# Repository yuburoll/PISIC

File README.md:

# PISIC
42-44key row staggered split keyboard with GRIN inspired layout, under 102mm PCB

The name PISIC means grin in korean, also is korean pun of grin layout of [ansic](https://github.com/yuburoll/ANSIC).

## Preparation

- 2x pro micro form factor dev board

- 2x PISIC PCB Boards, provided from the repo

- 1x printed case sets, 2 parts total, provided from the repo

- 2x 1.5-1.6T keyboard plates, provided from the repo

- 2x 1.5-1.6T back plates, provided from the repo

- 44x diodes

- 46x Kailh hotswap sockets (or compatibles)

- 24x M2x6 screws, flathead

- 2x PJ320A 1/8(3.5mm) TRRS connector

- 2x 4x4x1.5mm surface mount tact switches (if needed)

- 8x SK6812 Mini or WS2812b Mini (3535) RGB LED (if wanted)

- 1x 1/8(3.5mm) TRRS cable

- 0-2x PCB Mounted 2u Keyboard Stabilizers, normally 1 

- 42-44x MX Keyswitches, normally 43

- 8x 10mm bumpon stickers

- A set of Keycaps

## Build Guides and Miscellaneous

[**PISIC Build Guide**](documents/buildGuide.md)

there's some notices before the build:

- **You may solder all hotswaps before soldering the dev board.**

- Assemble dev board with 2.5mm height pin headers on back side, assume that components side are faced up.

- Jump every jumpers on front side.

- Assemble Case-Plate-Switch first, not Plate-Switch-PCB.

## Default Keymap

There are three more layers - Sym, Fn, Pad - which can be noticed by the color legends. ◇ Means Transparent; which uses base keymap.

Holding the color legend key swaps the layer.

## Licenses

all codes follow MIT license.

all designs and the hardware board follow CC BY-SA 4.0 license.

If you want to make a commercial product, it would be appreciated if you sponsor some bucks for me.

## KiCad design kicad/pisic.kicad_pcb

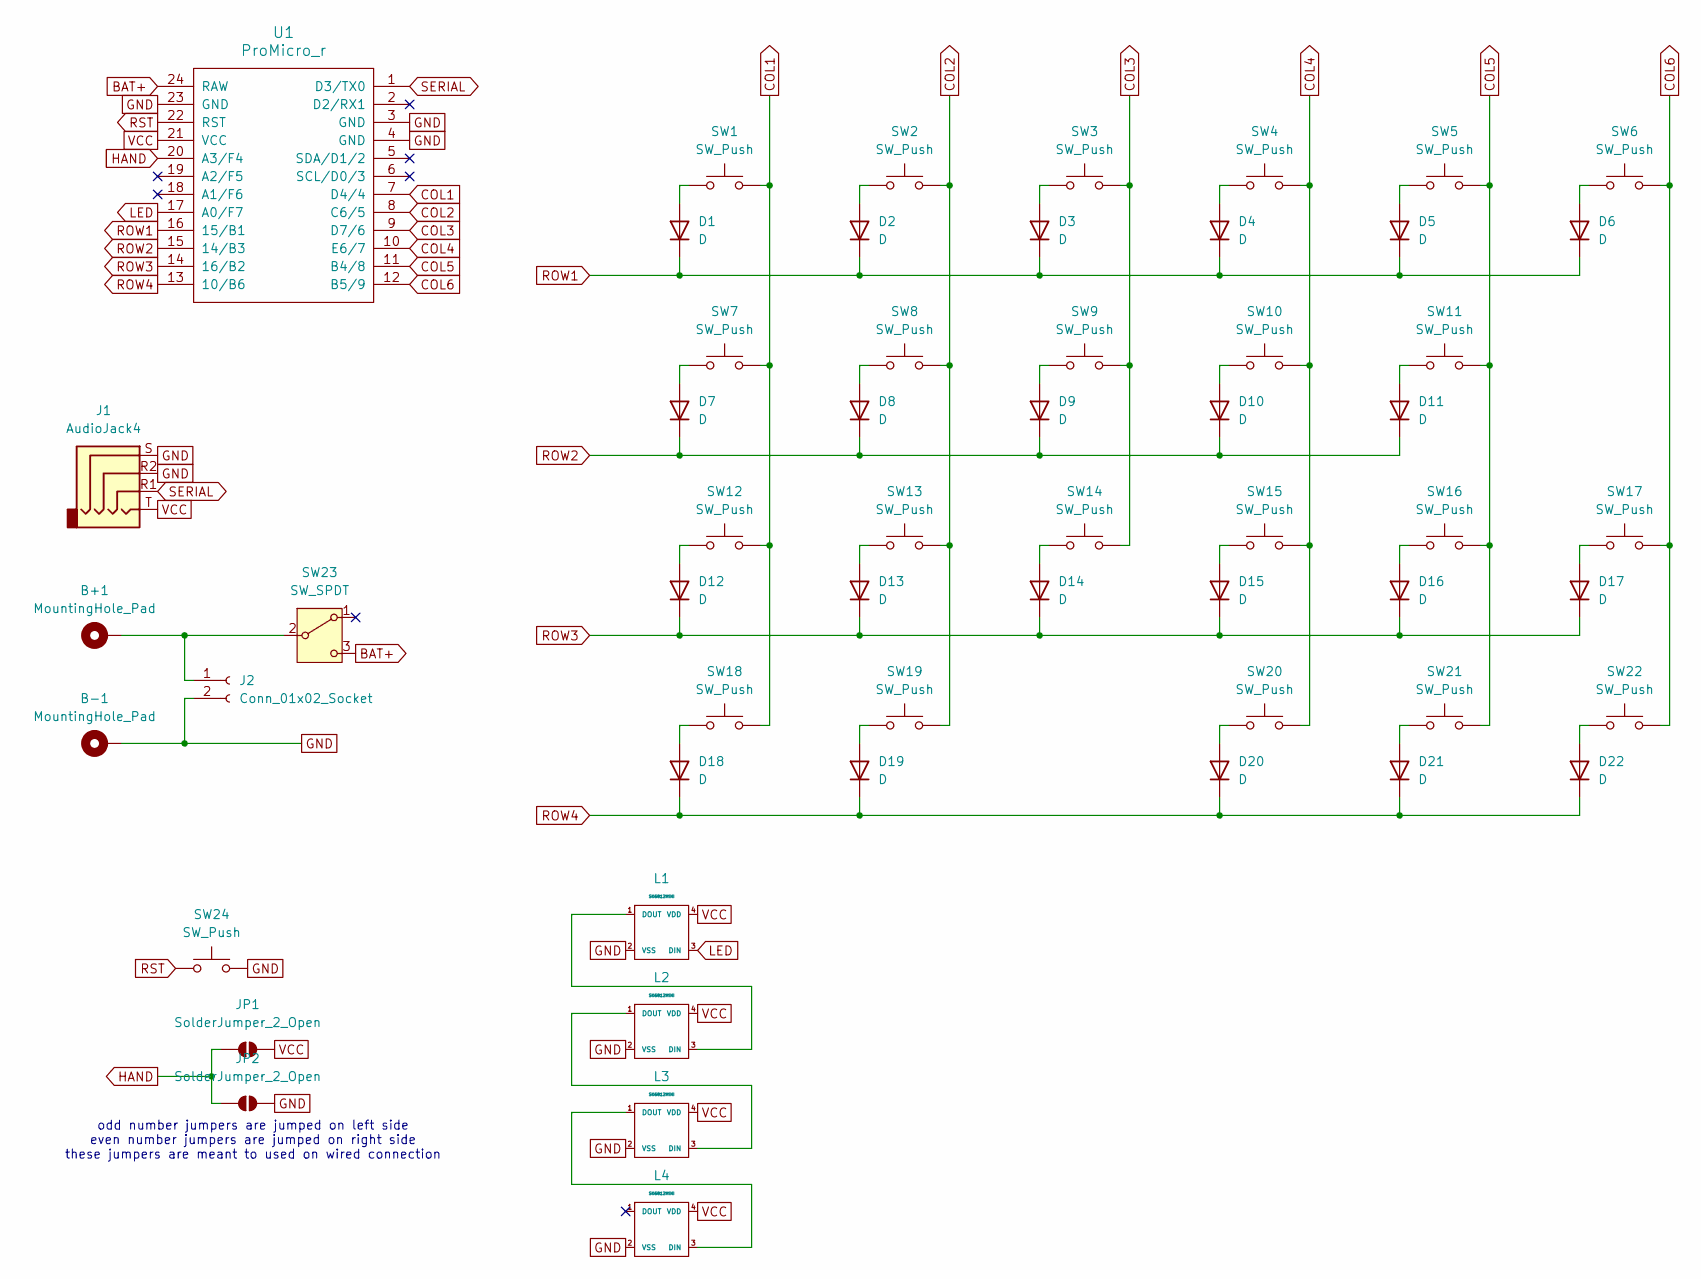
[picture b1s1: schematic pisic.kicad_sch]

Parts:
B+1: MountingHole_Pad
B-1: MountingHole_Pad
D1, D2, D3, D4, D5, D6, D7, D8, D9, D10, D11, D12, D13, D14, D15, D16, D17, D18, D19, D20, D21, D22: D
J1: AudioJack4
J2: Conn_01x02_Socket
JP1, JP2: SolderJumper_2_Open
L1, L2, L3, L4: SK6812MINI
SW1, SW2, SW3, SW4, SW5, SW6, SW7, SW8, SW9, SW10, SW11, SW12, SW13, SW14, SW15, SW16, SW17, SW18, SW19, SW20, SW21, SW22, SW24: SW_Push
SW23: SW_SPDT
U1: ProMicro_r

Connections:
BAT+: SW23.3 (C), U1.24 (RAW)
COL1: SW1.2, SW7.2, SW12.2, SW18.2, U1.7 (D4/4)
COL2: SW2.2, SW8.2, SW13.2, SW19.2, U1.8 (C6/5)
COL3: SW3.2, SW9.2, SW14.2, U1.9 (D7/6)
COL4: SW4.2, SW10.2, SW15.2, SW20.2, U1.10 (E6/7)
COL5: SW5.2, SW11.2, SW16.2, SW21.2, U1.11 (B4/8)
COL6: SW6.2, SW17.2, SW22.2, U1.12 (B5/9); also elsewhere on the board
GND: B-1.1, J1.R2, J1.S, J2.2, JP2.1 (A), L1.2 (VSS), L2.2 (VSS), L3.2 (VSS), L4.2 (VSS), SW23.SH, SW24.2, U1.3 (GND), U1.4 (GND), U1.23 (GND); also elsewhere on the board
HAND: JP1.2 (B), JP2.2 (B), U1.20 (A3/F4)
LED: L1.3 (DIN), U1.17 (A0/F7); also elsewhere on the board
unnamed: D1.2 (A), SW1.1
unnamed: D2.2 (A), SW2.1
unnamed: D3.2 (A), SW3.1
unnamed: D4.2 (A), SW4.1
unnamed: D5.2 (A), SW5.1
unnamed: D6.2 (A), SW6.1
unnamed: D7.2 (A), SW7.1
unnamed: D8.2 (A), SW8.1
unnamed: D9.2 (A), SW9.1
unnamed: D10.2 (A), SW10.1
unnamed: D11.2 (A), SW11.1
unnamed: D12.2 (A), SW12.1
unnamed: D13.2 (A), SW13.1
unnamed: D14.2 (A), SW14.1
unnamed: D15.2 (A), SW15.1
unnamed: D16.2 (A), SW16.1
unnamed: D17.2 (A), SW17.1
unnamed: D18.2 (A), SW18.1
unnamed: D19.2 (A), SW19.1
unnamed: D20.2 (A), SW20.1
unnamed: D21.2 (A), SW21.1
unnamed 31: D22.2 (A), SW22.1; also elsewhere on the board
unnamed: B+1.1, J2.1, SW23.2 (B)
unnamed 33: L1.1 (DOUT), L2.3 (DIN); also elsewhere on the board
unnamed 34: L2.1 (DOUT), L3.3 (DIN); also elsewhere on the board
unnamed 35: L3.1 (DOUT), L4.3 (DIN); also elsewhere on the board
ROW1: D1.1 (K), D2.1 (K), D3.1 (K), D4.1 (K), D5.1 (K), D6.1 (K), U1.16 (15/B1)
ROW2: D7.1 (K), D8.1 (K), D9.1 (K), D10.1 (K), D11.1 (K), U1.15 (14/B3)
ROW3: D12.1 (K), D13.1 (K), D14.1 (K), D15.1 (K), D16.1 (K), D17.1 (K), U1.14 (16/B2)
ROW4: D18.1 (K), D19.1 (K), D20.1 (K), D21.1 (K), D22.1 (K), U1.13 (10/B6)
RST: SW24.1, U1.22 (RST); also elsewhere on the board
SERIAL: J1.R1, U1.1 (D3/TX0)
VCC: J1.T, JP1.1 (A), L1.4 (VDD), L2.4 (VDD), L3.4 (VDD), L4.4 (VDD), U1.21 (VCC); also elsewhere on the board

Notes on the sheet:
odd number jumpers are jumped on left side even number jumpers are jumped on right side these jumpers are meant to used on wired connection

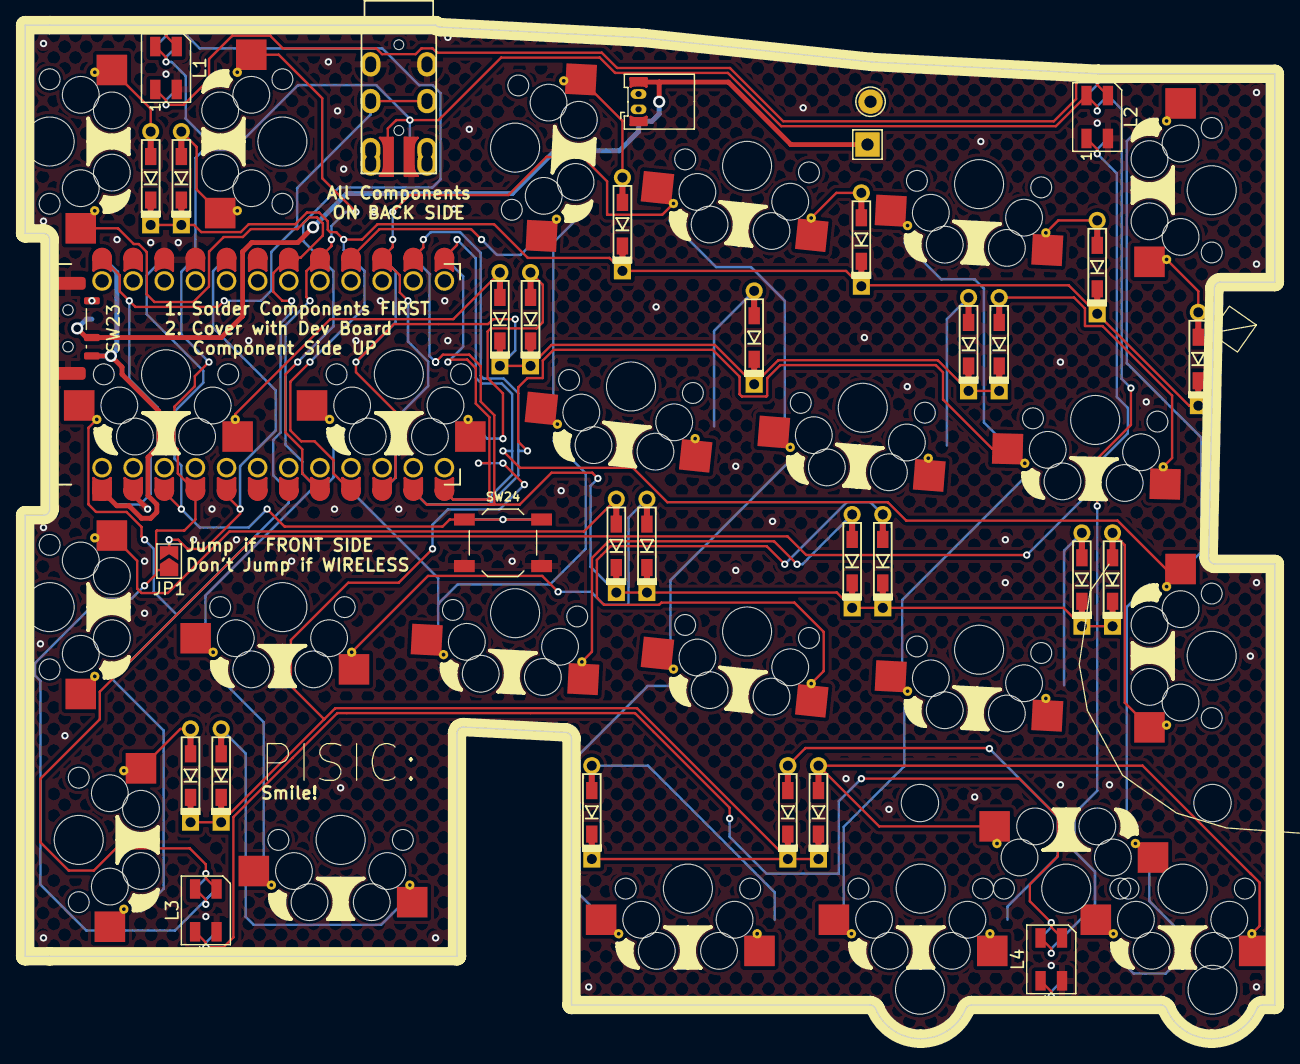
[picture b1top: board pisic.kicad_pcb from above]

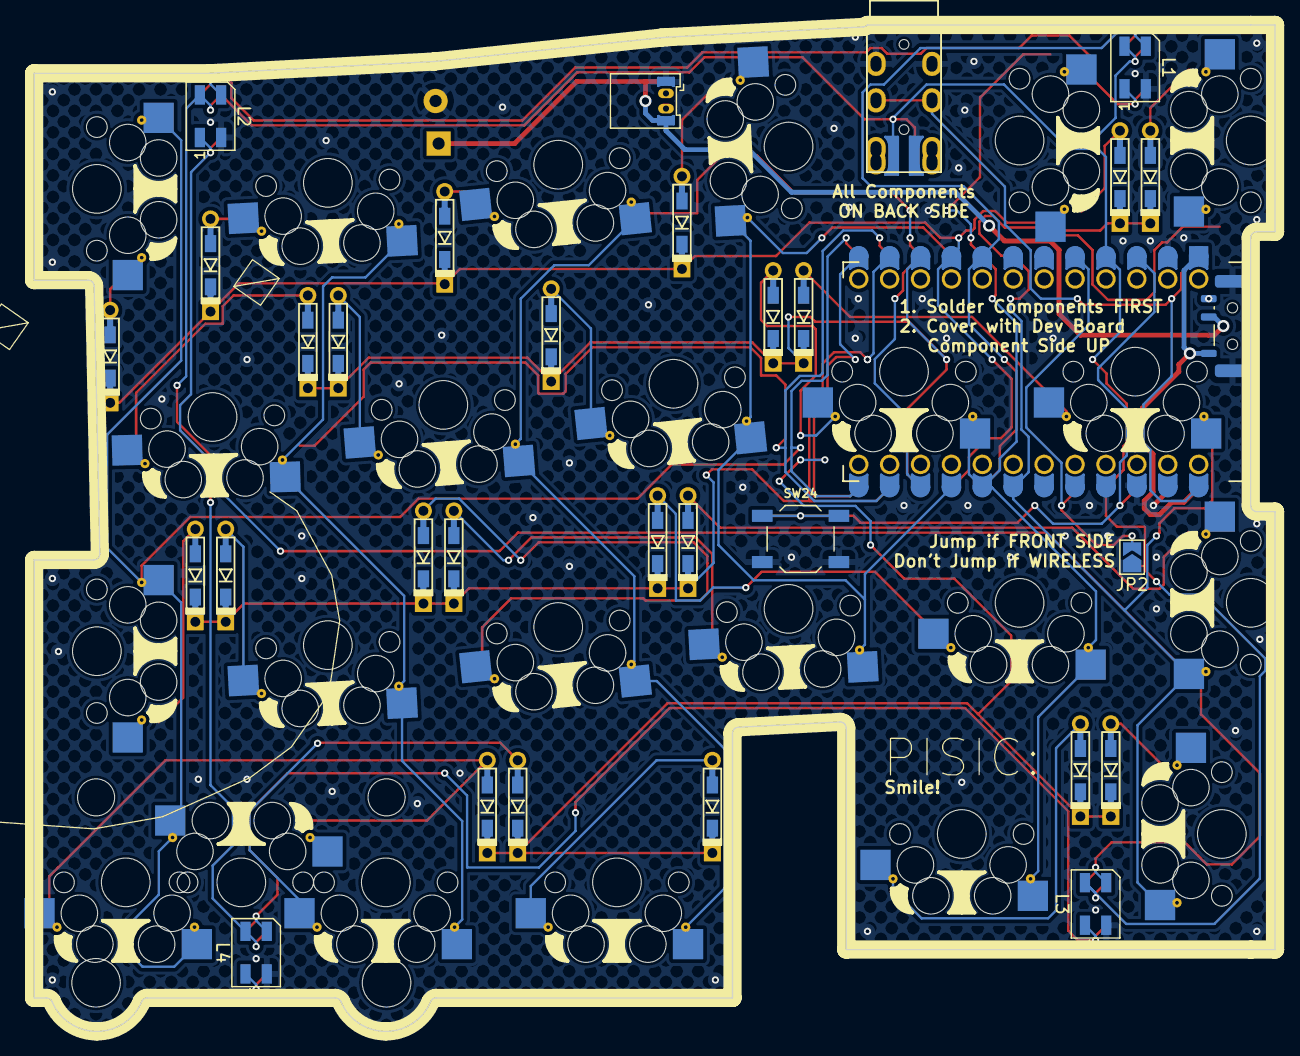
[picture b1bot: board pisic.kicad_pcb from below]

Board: 2 copper layers, 102.0 x 82.7 mm, 63 parts (6 on the bottom side), 43 nets.

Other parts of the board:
L1#2, L2#2, L3#2, L4#2: SK6812MINI; LED_SK6812MINI_PLCC4_3.5x3.5mm_P1.75mm
SW22#2: SW_Push; MX_Hotswap_FootprintPropertyFix_Guided
SW24#2: SW_Push; SW_SPST_TL3342

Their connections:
COL6: SW22#2.2; also elsewhere on the board
GND: L1#2.2 (VSS), L2#2.2 (VSS), L3#2.2 (VSS), L4#2.2 (VSS), SW24#2.2; also elsewhere on the board
LED: L1#2.3 (DIN); also elsewhere on the board
unnamed 31: SW22#2.1; also elsewhere on the board
unnamed 33: L1#2.1 (DOUT), L2#2.3 (DIN); also elsewhere on the board
unnamed 34: L2#2.1 (DOUT), L3#2.3 (DIN); also elsewhere on the board
unnamed 35: L3#2.1 (DOUT), L4#2.3 (DIN); also elsewhere on the board
RST: SW24#2.1; also elsewhere on the board
VCC: L1#2.4 (VDD), L2#2.4 (VDD), L3#2.4 (VDD), L4#2.4 (VDD); also elsewhere on the board

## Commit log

2026-04-23 change case design and add bridge for backplate
2026-04-26 edit keymap with keypads
2026-04-26 change some typo of keymaps
2026-04-27 add images, prepare for build guide
2026-04-27 finish buildguide and readme
2026-04-27 Rename buildguide.md to buildGuide.md
2026-04-27 change profile image
2026-04-27 add case 3mf variants
2026-04-28 tweaked pcb for some space
2026-04-28 rgb tweak and polish keymap
2026-04-28 edited ground pour design
2026-04-28 fix typo of keymap
2026-04-28 enhance case: enforced fragile corner screws. also edited plates
2026-04-29 add image of finished pcb for buildguide
